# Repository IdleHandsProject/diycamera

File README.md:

# digiOBSCURA - A DIY Image Sensor and Digital Camera!

Check out the video!

Find the BOM for both boards here: https://www.findchips.com/org/10-open-hardware/list/162969-digiobscura-diy-image-sensor-and-digital-camera

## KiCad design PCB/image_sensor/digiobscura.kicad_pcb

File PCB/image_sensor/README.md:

# TEMPLATE KICAD PROJECT
## Sean Hodgins

If you're reading this, it means I have started a new project but have neglected to update the README file.
Please notify me of this by any means possible. 

Twitter: @idlehandsdev
Instagram: @idlehandsdev

Since you're reading this, go check out my YouTube Channel! http://youtube.com/seanhodginsfilms

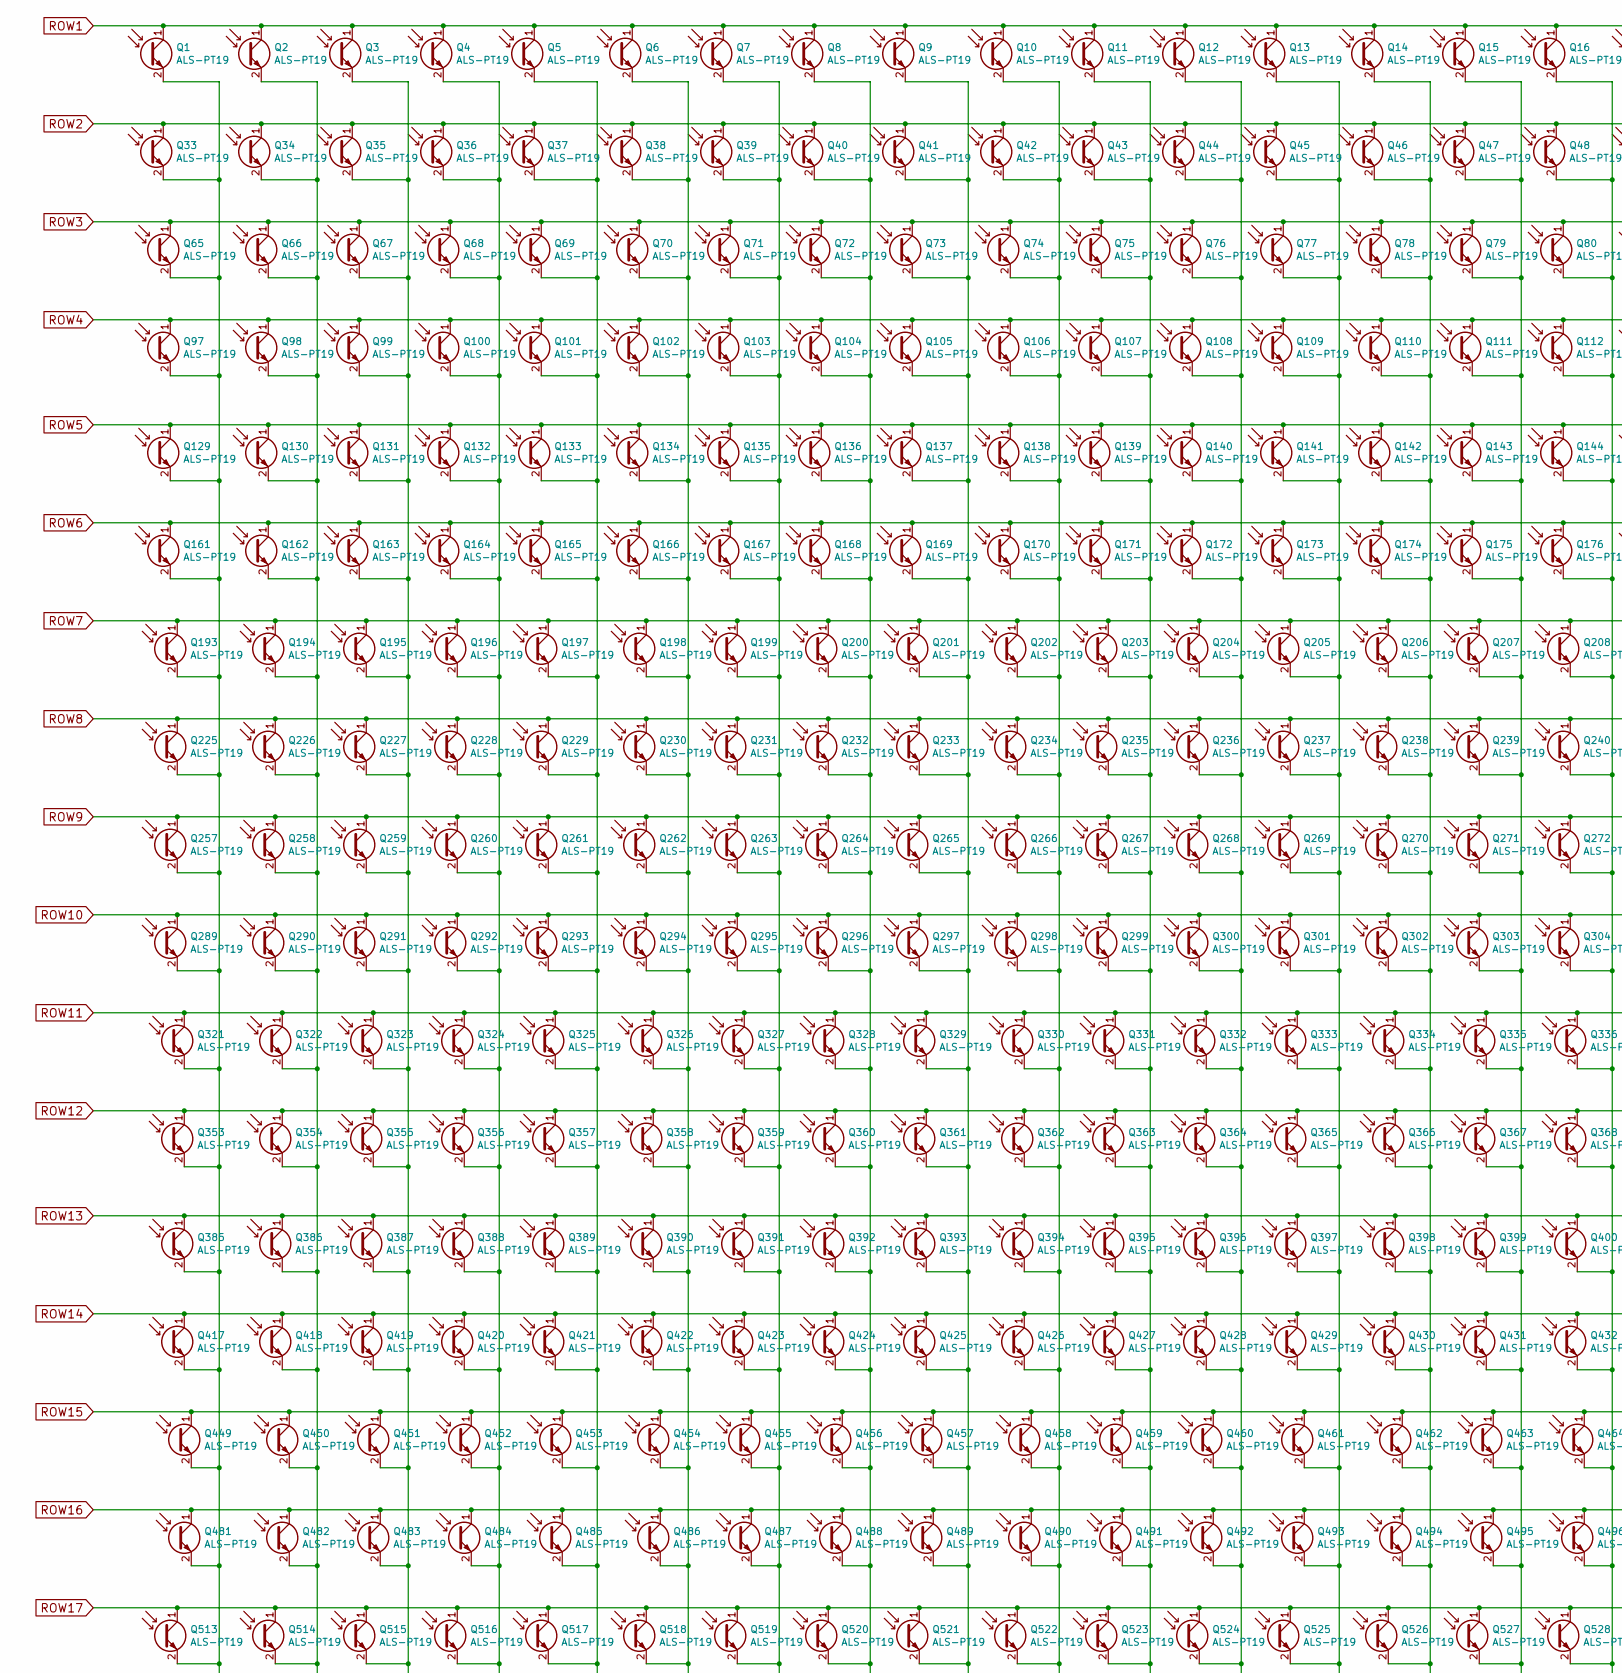
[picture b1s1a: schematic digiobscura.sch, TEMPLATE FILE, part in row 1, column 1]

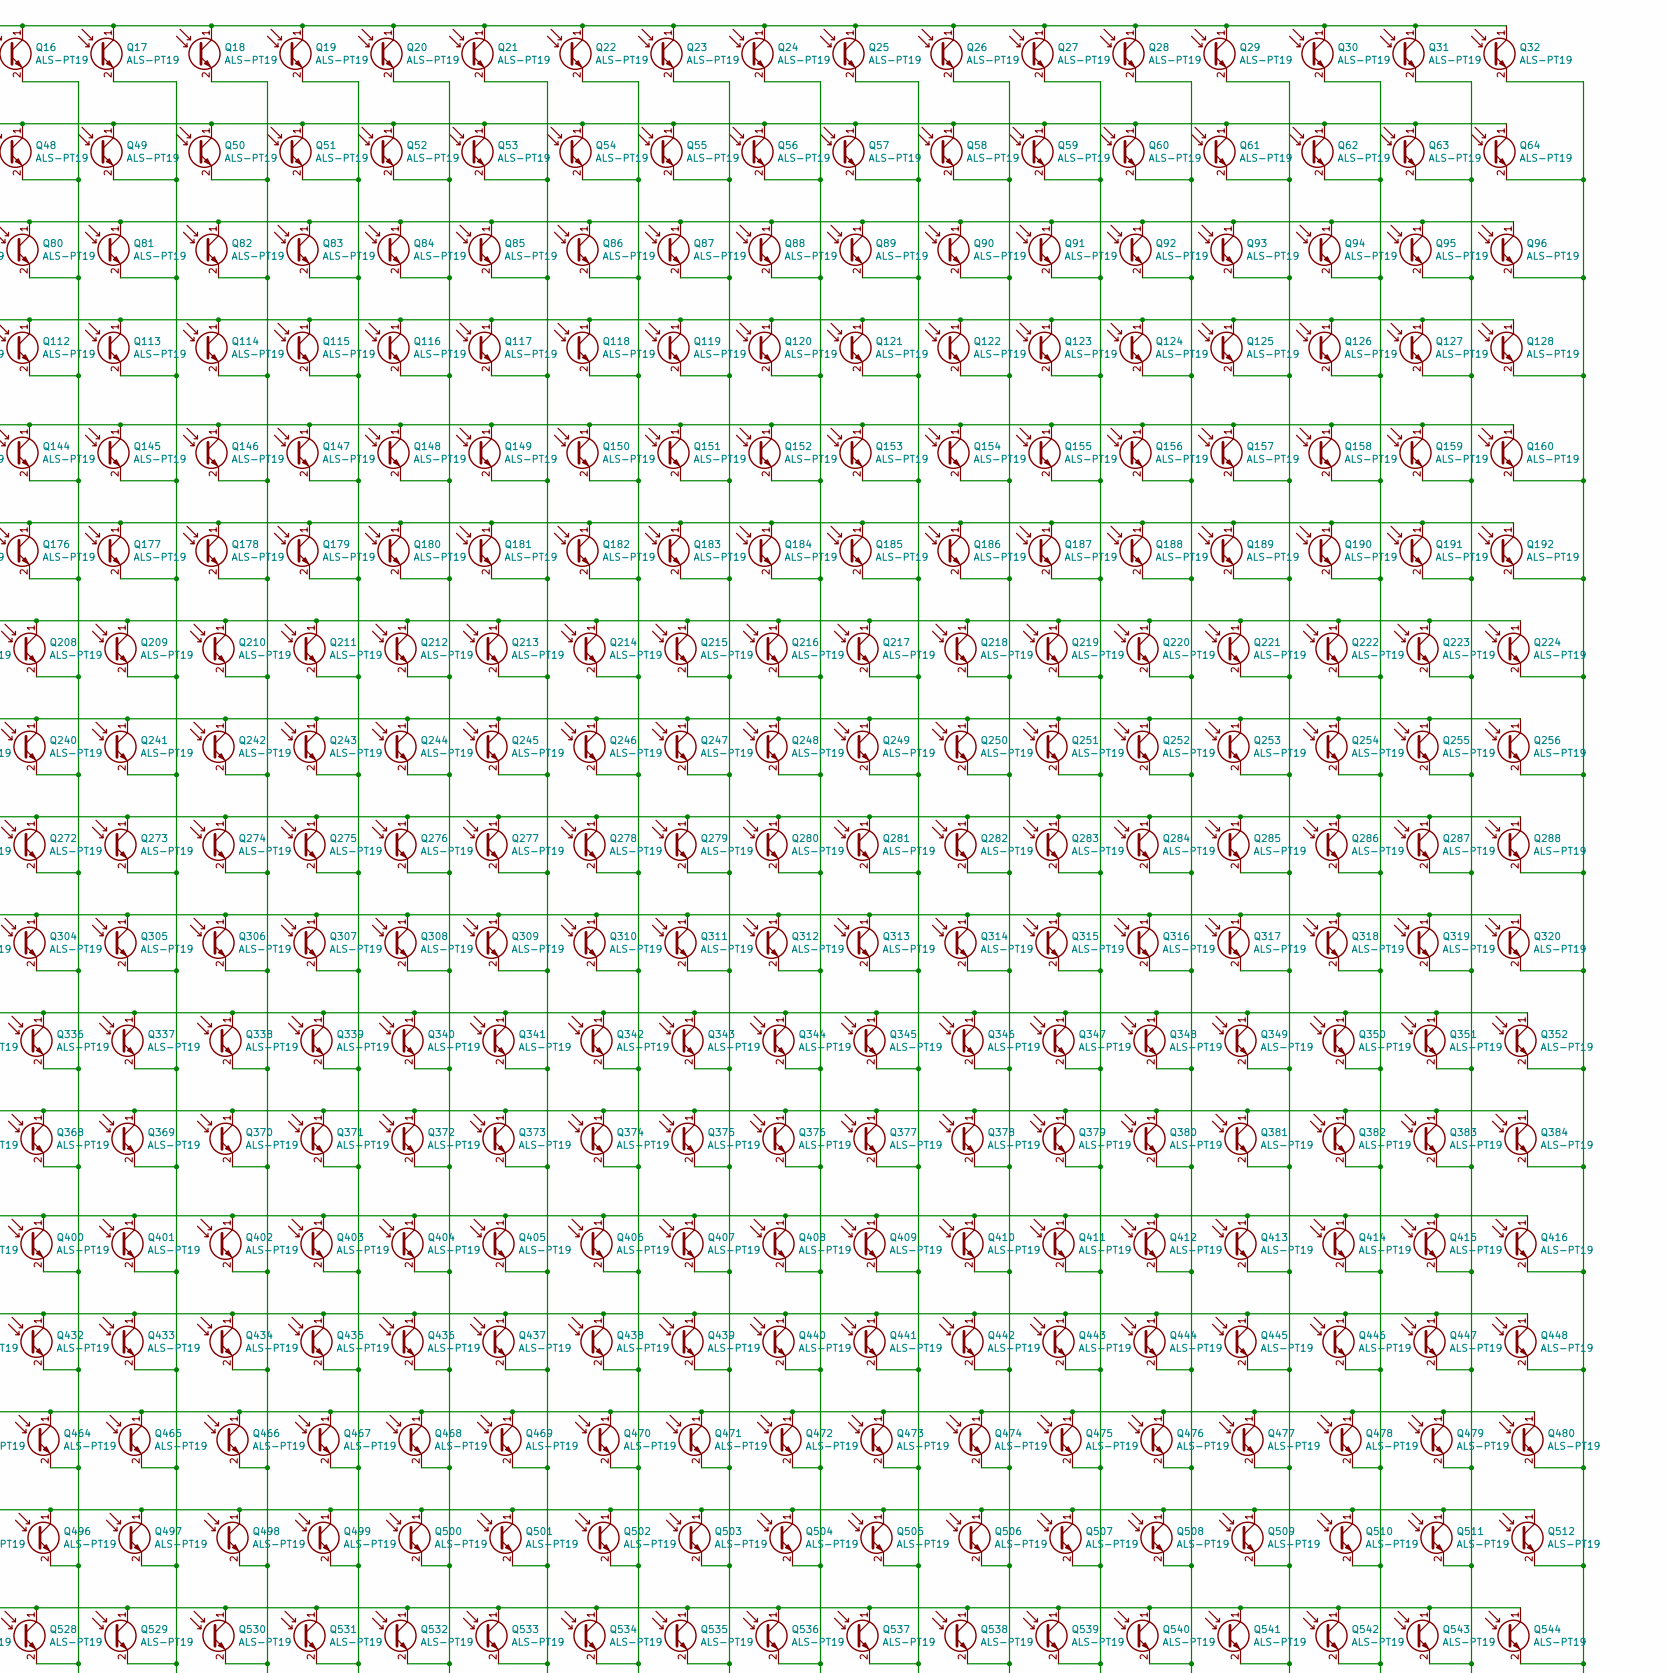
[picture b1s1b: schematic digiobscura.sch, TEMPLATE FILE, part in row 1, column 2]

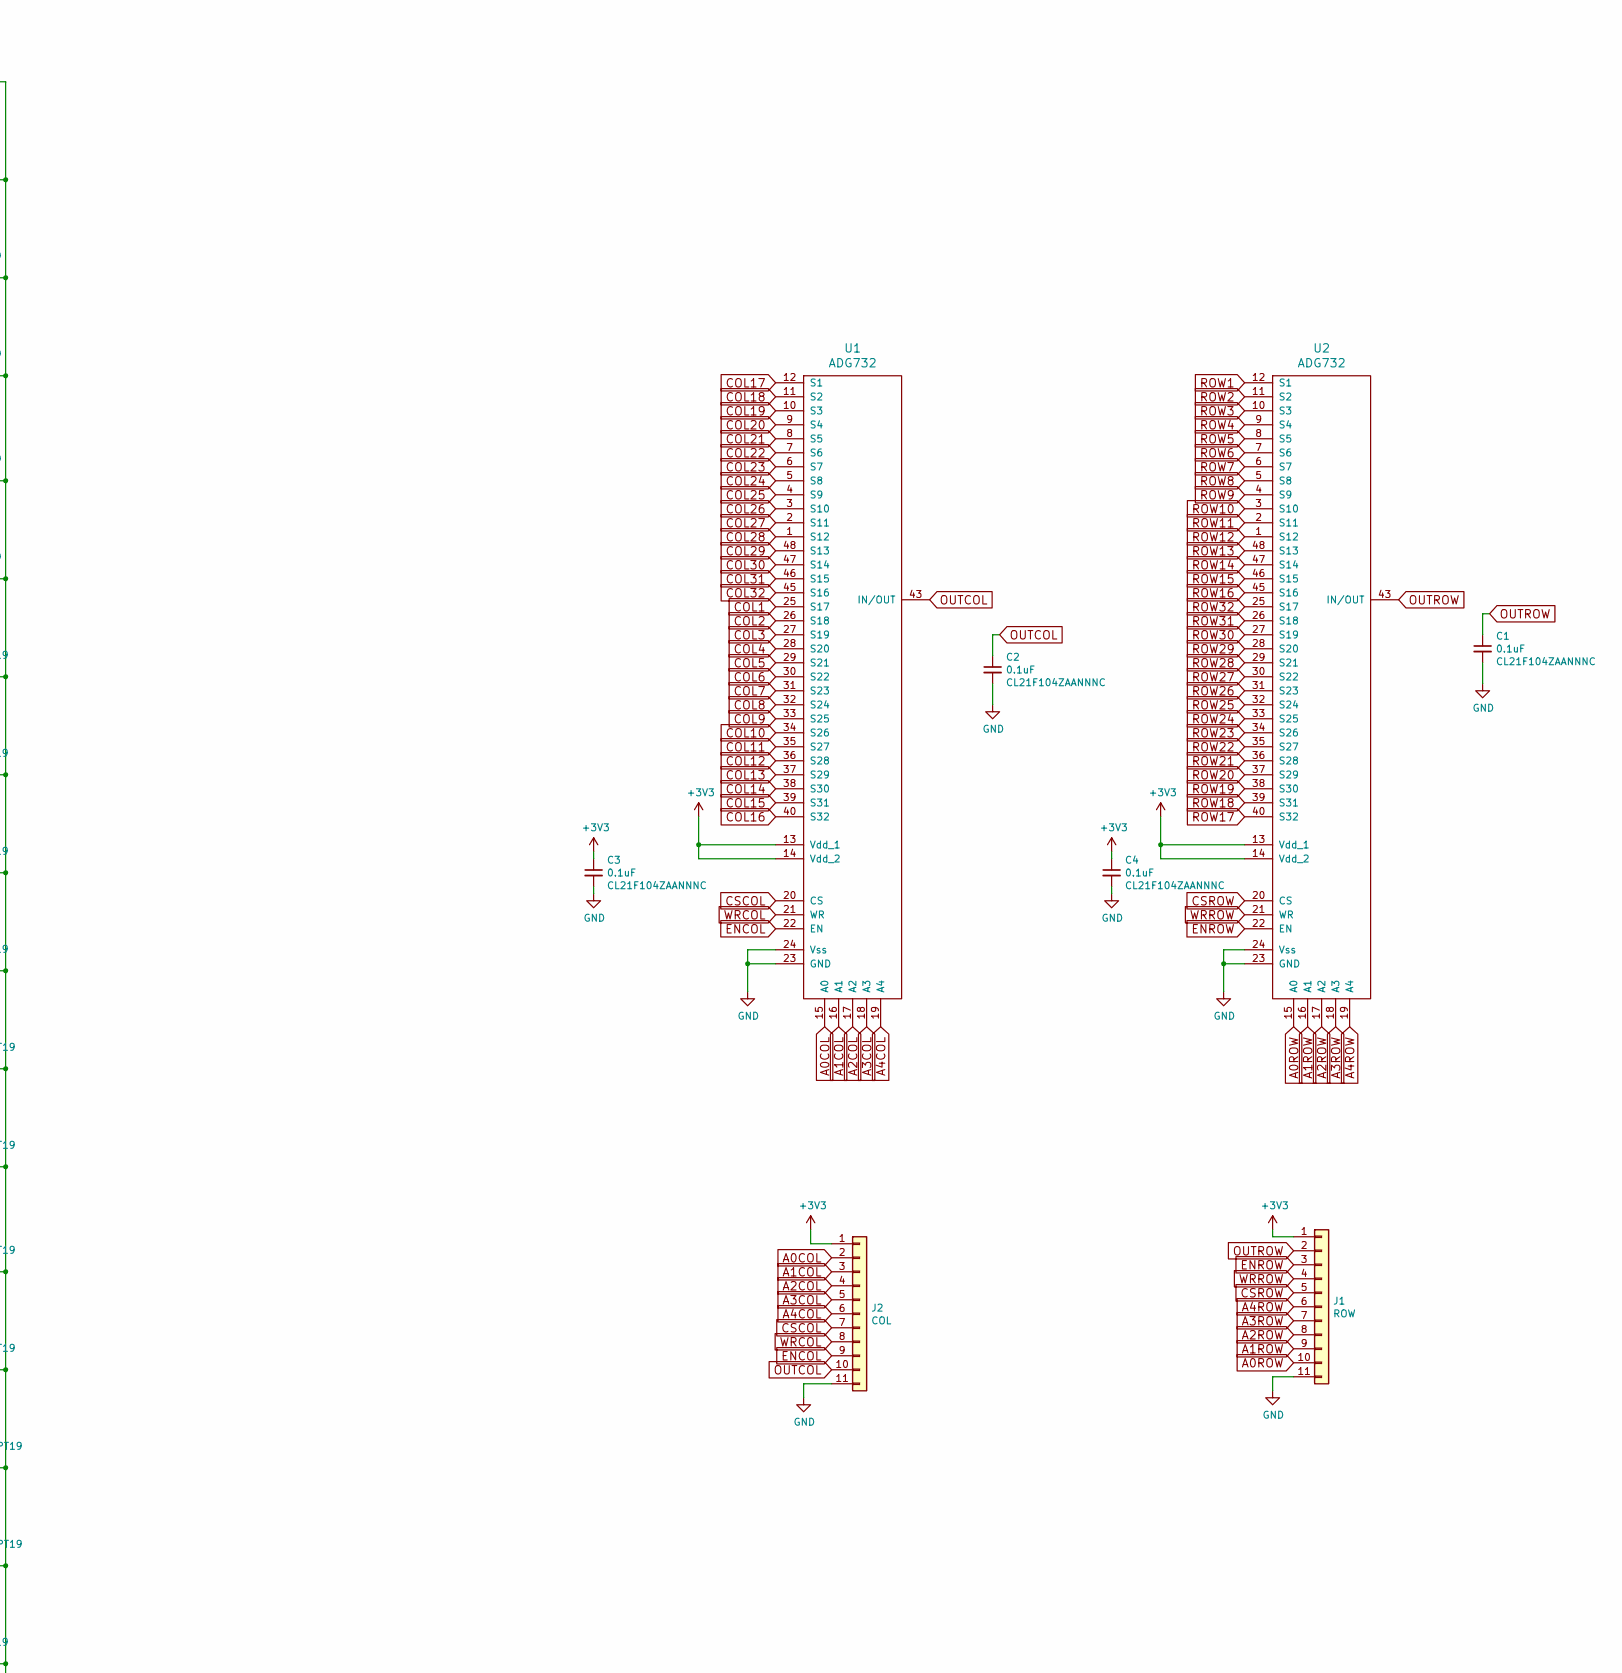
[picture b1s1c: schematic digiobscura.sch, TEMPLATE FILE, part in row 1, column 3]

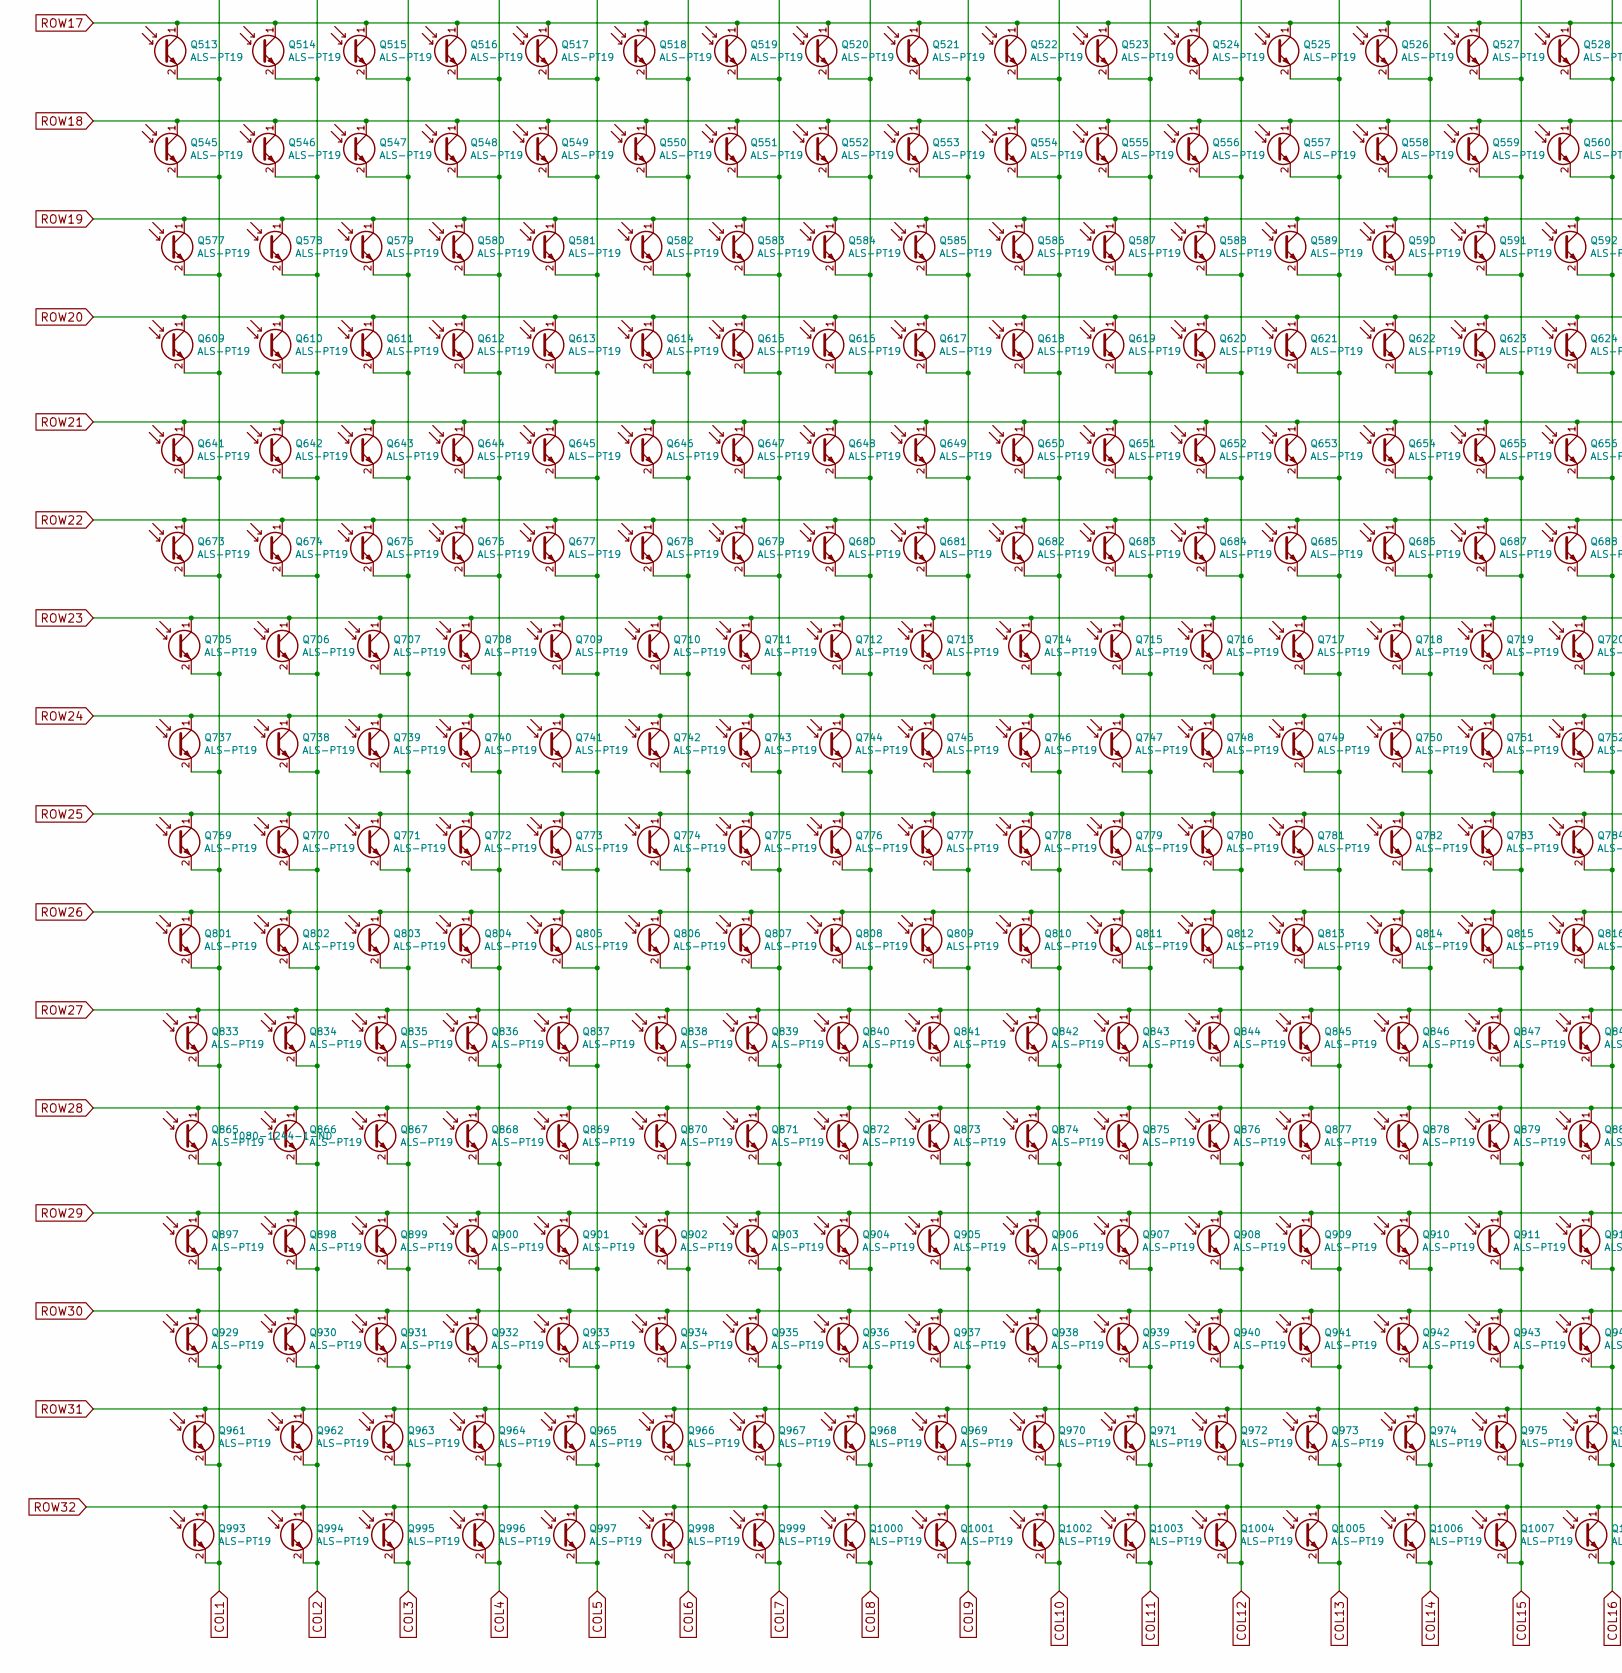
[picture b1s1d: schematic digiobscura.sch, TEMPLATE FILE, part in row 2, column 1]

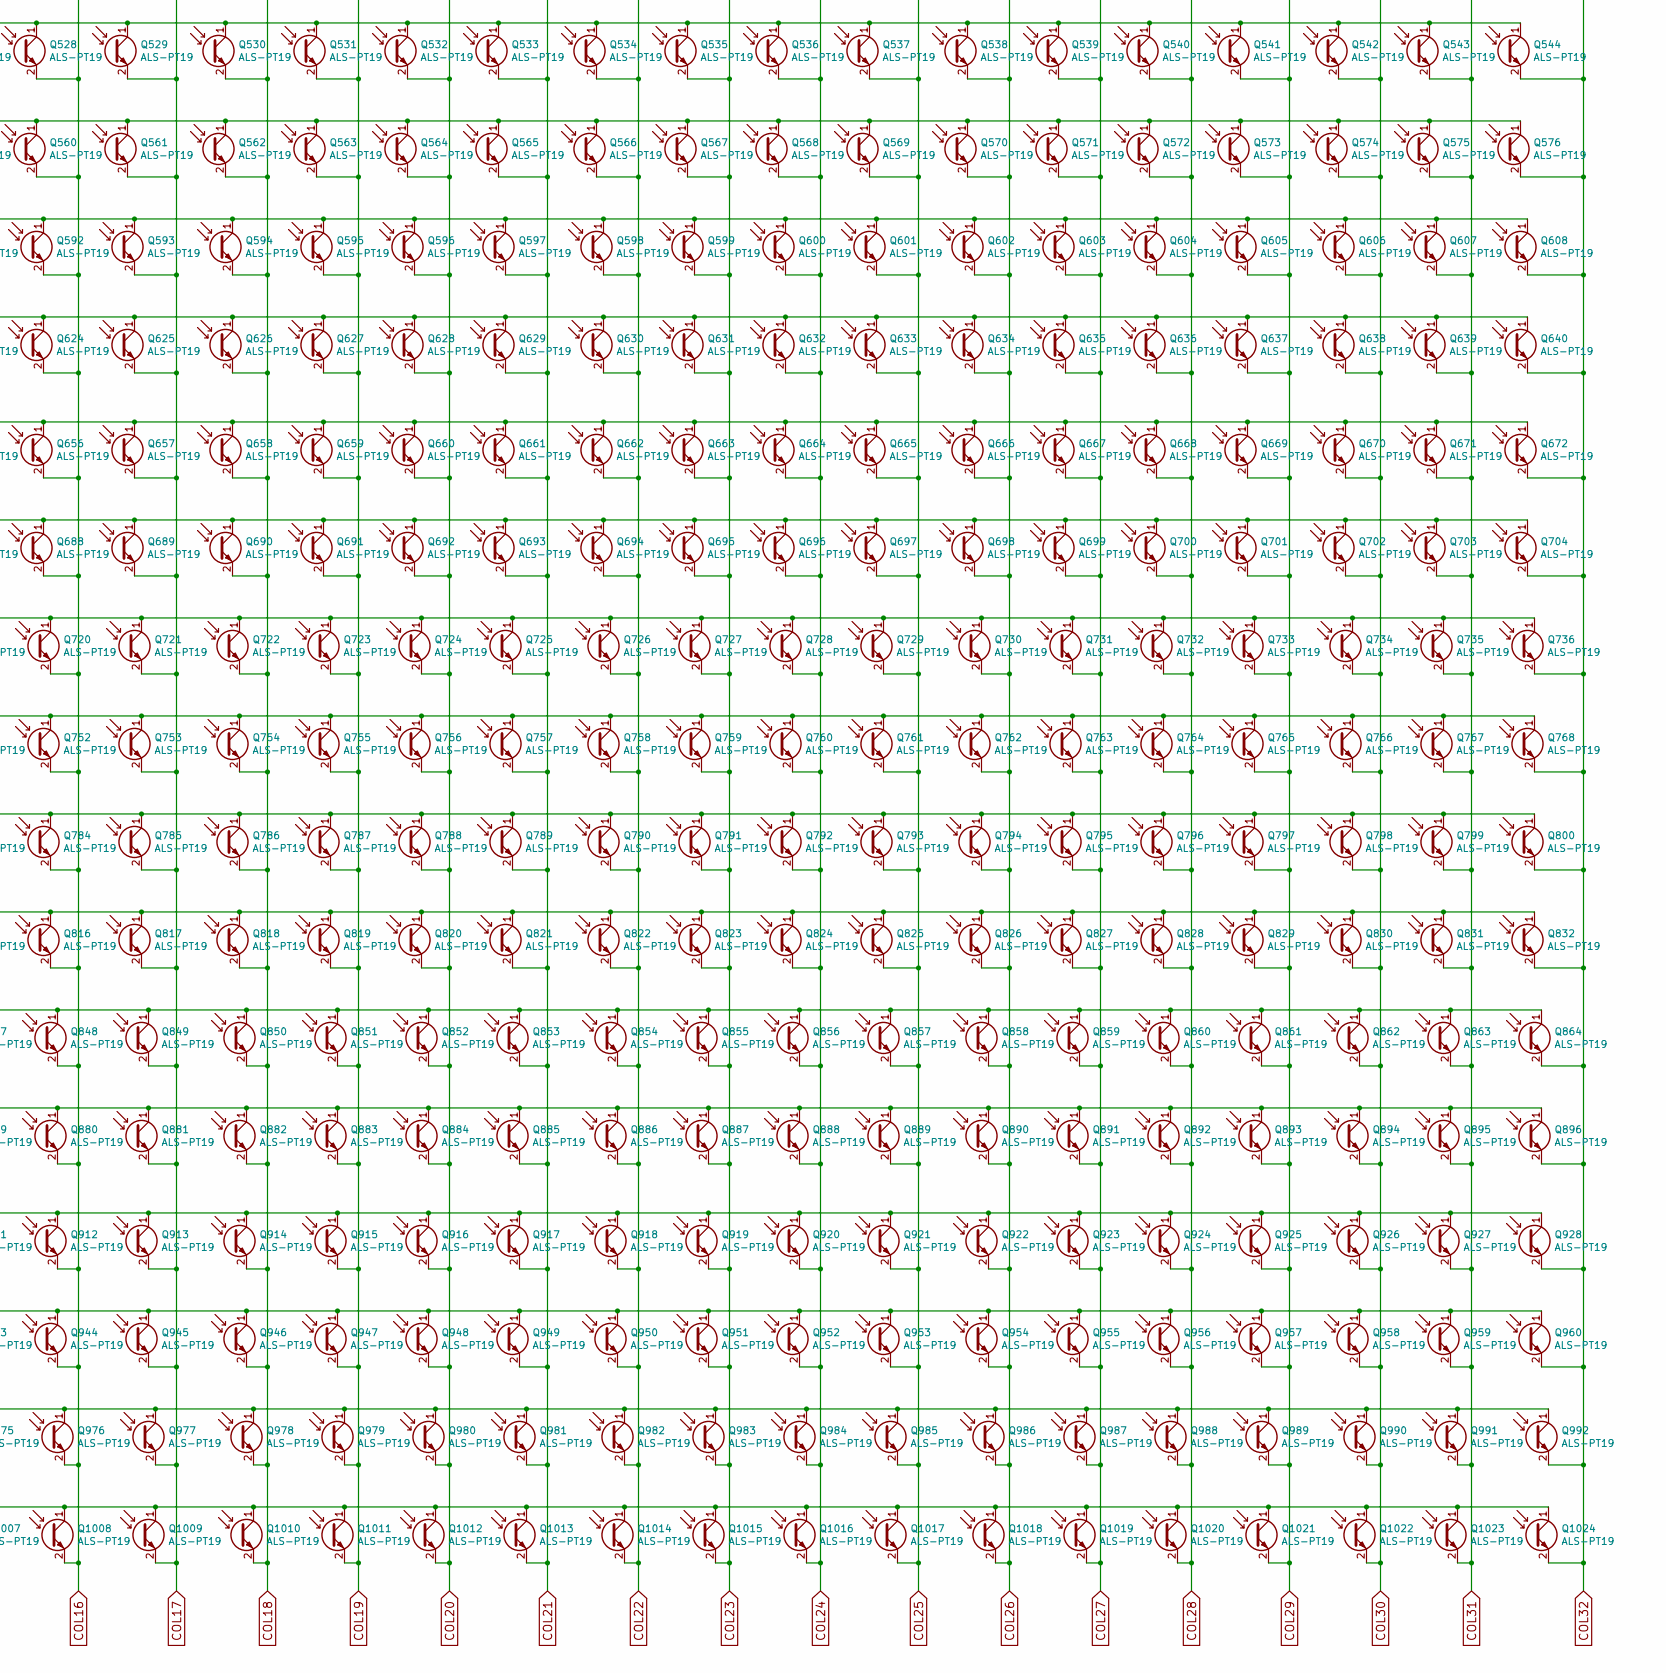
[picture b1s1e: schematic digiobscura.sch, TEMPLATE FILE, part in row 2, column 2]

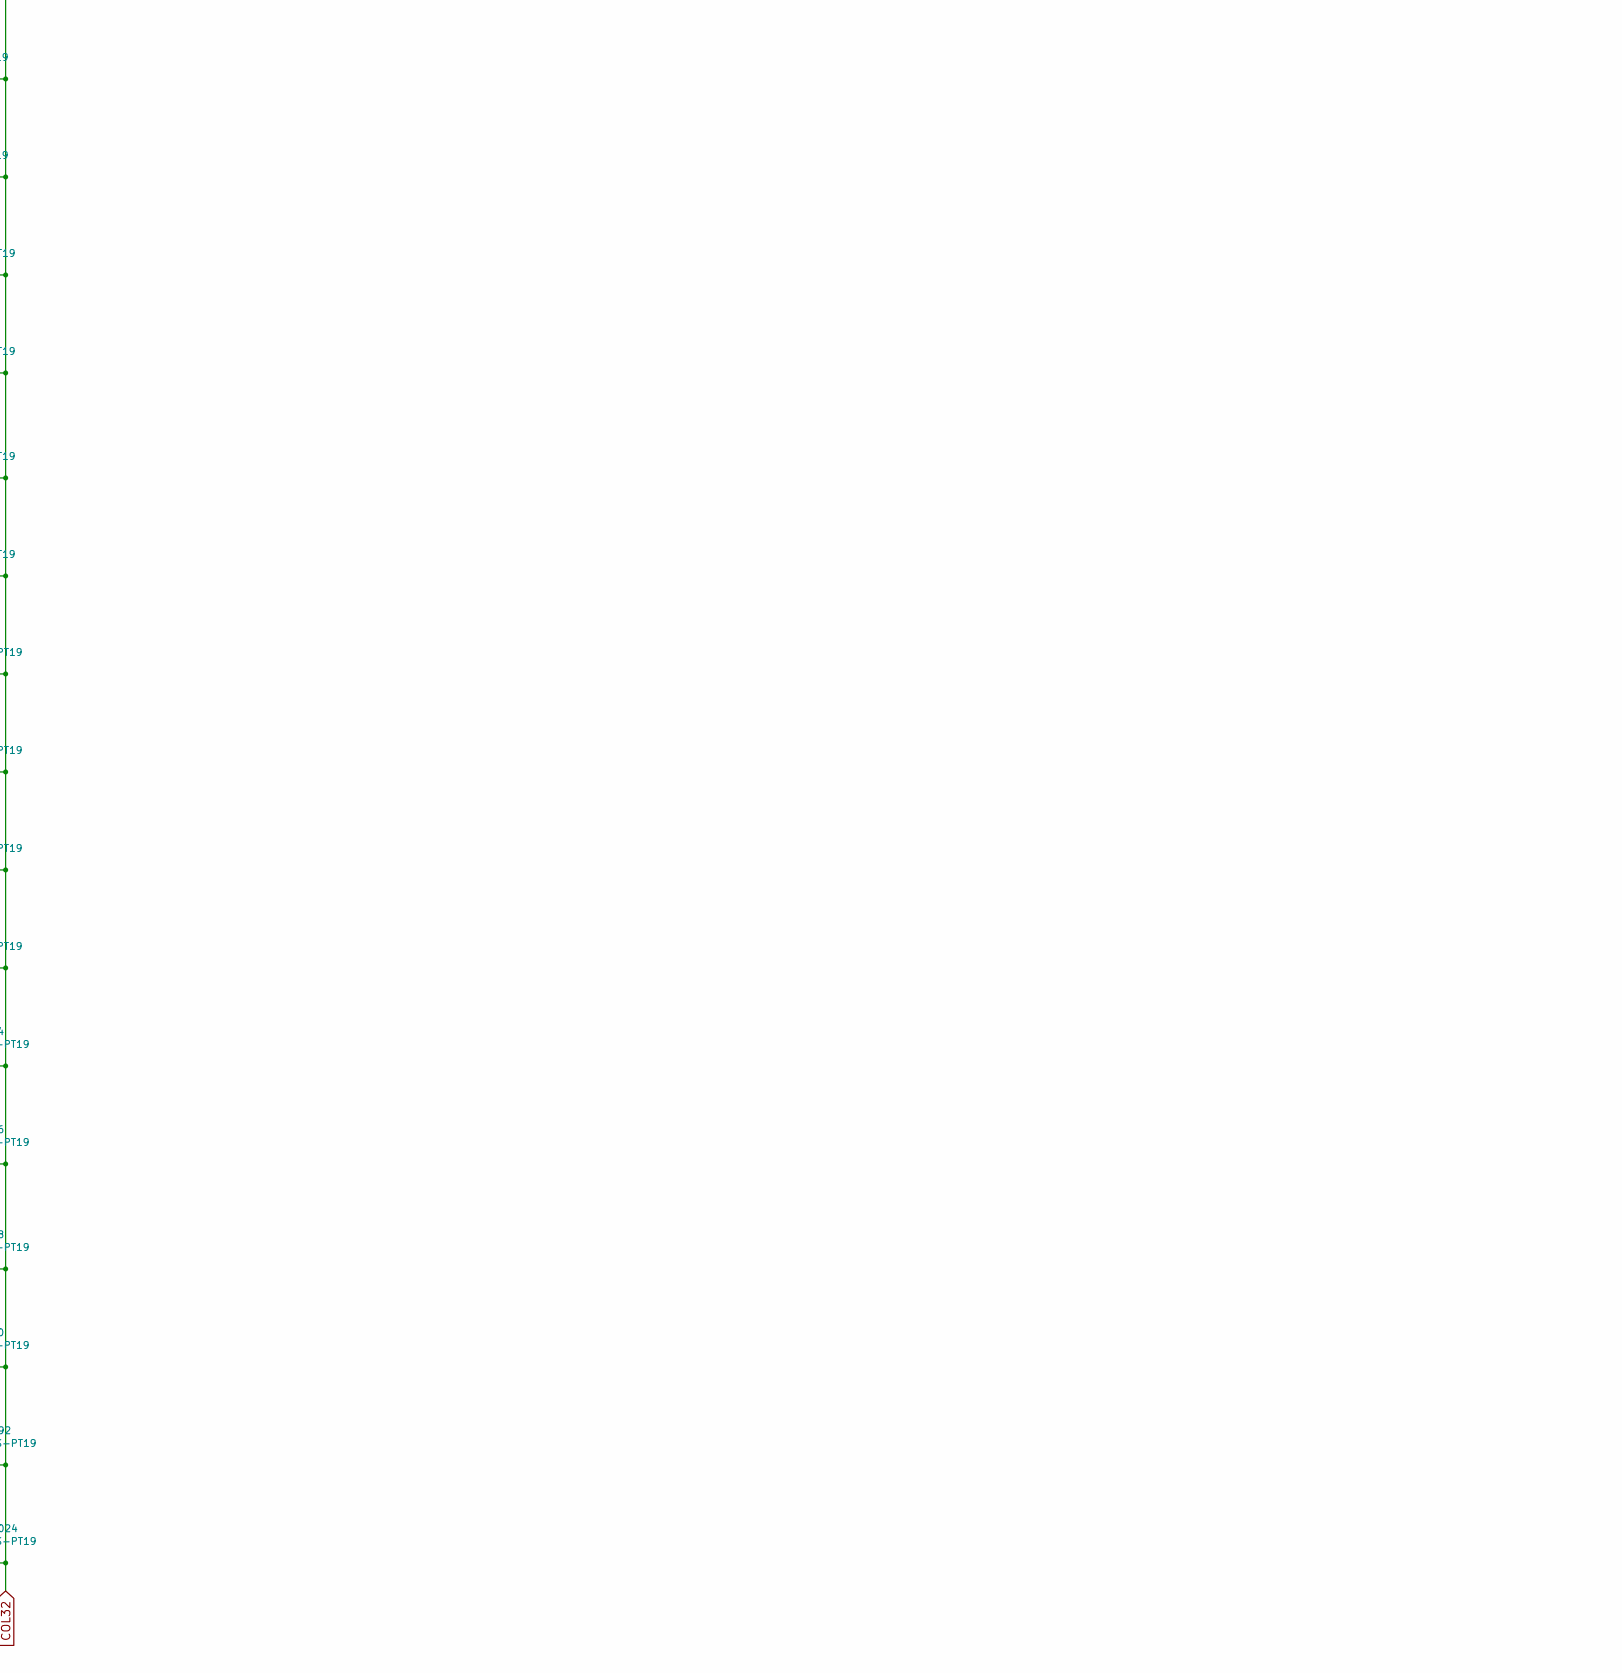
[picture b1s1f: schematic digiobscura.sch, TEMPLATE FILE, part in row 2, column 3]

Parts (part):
C1, C2, C3, C4: 0.1uF; C_0805_2012Metric; Digikey Part No. CL21F104ZAANNNC
J1: ROW; PinHeader_1x11_P2.54mm_Vertical; Digikey Part No. S7044-ND
J2: COL; PinHeader_1x11_P2.54mm_Vertical; Digikey Part No. S7044-ND
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
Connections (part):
+3V3: C3.1, C4.1, J1.1, J2.1, U1.13 (Vdd_1), U1.14 (Vdd_2), U2.13 (Vdd_1), U2.14 (Vdd_2)
A0COL: J2.2, U1.15 (A0)
A0ROW: J1.10, U2.15 (A0)
A1COL: J2.3, U1.16 (A1)
A1ROW: J1.9, U2.16 (A1)
A2COL: J2.4, U1.17 (A2)
A2ROW: J1.8, U2.17 (A2)
A3COL: J2.5, U1.18 (A3)
A3ROW: J1.7, U2.18 (A3)
A4COL: J2.6, U1.19 (A4)
A4ROW: J1.6, U2.19 (A4)
COL1: Q1.2 (E), Q33.2 (E), Q65.2 (E), Q97.2 (E), Q129.2 (E), Q161.2 (E), Q193.2 (E), Q225.2 (E), Q257.2 (E), Q289.2 (E), Q321.2 (E), Q353.2 (E), Q385.2 (E), Q417.2 (E), Q449.2 (E), Q481.2 (E), Q513.2 (E), Q545.2 (E), Q577.2 (E), Q609.2 (E), Q641.2 (E), Q673.2 (E), Q705.2 (E), Q737.2 (E), Q769.2 (E), Q801.2 (E), Q833.2 (E), Q865.2 (E), Q897.2 (E), Q929.2 (E), Q961.2 (E), Q993.2 (E), U1.25 (S17)
COL2: Q2.2 (E), Q34.2 (E), Q66.2 (E), Q98.2 (E), Q130.2 (E), Q162.2 (E), Q194.2 (E), Q226.2 (E), Q258.2 (E), Q290.2 (E), Q322.2 (E), Q354.2 (E), Q386.2 (E), Q418.2 (E), Q450.2 (E), Q482.2 (E), Q514.2 (E), Q546.2 (E), Q578.2 (E), Q610.2 (E), Q642.2 (E), Q674.2 (E), Q706.2 (E), Q738.2 (E), Q770.2 (E), Q802.2 (E), Q834.2 (E), Q866.2 (E), Q898.2 (E), Q930.2 (E), Q962.2 (E), Q994.2 (E), U1.26 (S18)
COL3: Q3.2 (E), Q35.2 (E), Q67.2 (E), Q99.2 (E), Q131.2 (E), Q163.2 (E), Q195.2 (E), Q227.2 (E), Q259.2 (E), Q291.2 (E), Q323.2 (E), Q355.2 (E), Q387.2 (E), Q419.2 (E), Q451.2 (E), Q483.2 (E), Q515.2 (E), Q547.2 (E), Q579.2 (E), Q611.2 (E), Q643.2 (E), Q675.2 (E), Q707.2 (E), Q739.2 (E), Q771.2 (E), Q803.2 (E), Q835.2 (E), Q867.2 (E), Q899.2 (E), Q931.2 (E), Q963.2 (E), Q995.2 (E), U1.27 (S19)
COL4: Q4.2 (E), Q36.2 (E), Q68.2 (E), Q100.2 (E), Q132.2 (E), Q164.2 (E), Q196.2 (E), Q228.2 (E), Q260.2 (E), Q292.2 (E), Q324.2 (E), Q356.2 (E), Q388.2 (E), Q420.2 (E), Q452.2 (E), Q484.2 (E), Q516.2 (E), Q548.2 (E), Q580.2 (E), Q612.2 (E), Q644.2 (E), Q676.2 (E), Q708.2 (E), Q740.2 (E), Q772.2 (E), Q804.2 (E), Q836.2 (E), Q868.2 (E), Q900.2 (E), Q932.2 (E), Q964.2 (E), Q996.2 (E), U1.28 (S20)
COL5: Q5.2 (E), Q37.2 (E), Q69.2 (E), Q101.2 (E), Q133.2 (E), Q165.2 (E), Q197.2 (E), Q229.2 (E), Q261.2 (E), Q293.2 (E), Q325.2 (E), Q357.2 (E), Q389.2 (E), Q421.2 (E), Q453.2 (E), Q485.2 (E), Q517.2 (E), Q549.2 (E), Q581.2 (E), Q613.2 (E), Q645.2 (E), Q677.2 (E), Q709.2 (E), Q741.2 (E), Q773.2 (E), Q805.2 (E), Q837.2 (E), Q869.2 (E), Q901.2 (E), Q933.2 (E), Q965.2 (E), Q997.2 (E), U1.29 (S21)
COL6: Q6.2 (E), Q38.2 (E), Q70.2 (E), Q102.2 (E), Q134.2 (E), Q166.2 (E), Q198.2 (E), Q230.2 (E), Q262.2 (E), Q294.2 (E), Q326.2 (E), Q358.2 (E), Q390.2 (E), Q422.2 (E), Q454.2 (E), Q486.2 (E), Q518.2 (E), Q550.2 (E), Q582.2 (E), Q614.2 (E), Q646.2 (E), Q678.2 (E), Q710.2 (E), Q742.2 (E), Q774.2 (E), Q806.2 (E), Q838.2 (E), Q870.2 (E), Q902.2 (E), Q934.2 (E), Q966.2 (E), Q998.2 (E), U1.30 (S22)
COL7: Q7.2 (E), Q39.2 (E), Q71.2 (E), Q103.2 (E), Q135.2 (E), Q167.2 (E), Q199.2 (E), Q231.2 (E), Q263.2 (E), Q295.2 (E), Q327.2 (E), Q359.2 (E), Q391.2 (E), Q423.2 (E), Q455.2 (E), Q487.2 (E), Q519.2 (E), Q551.2 (E), Q583.2 (E), Q615.2 (E), Q647.2 (E), Q679.2 (E), Q711.2 (E), Q743.2 (E), Q775.2 (E), Q807.2 (E), Q839.2 (E), Q871.2 (E), Q903.2 (E), Q935.2 (E), Q967.2 (E), Q999.2 (E), U1.31 (S23)
COL8: Q8.2 (E), Q40.2 (E), Q72.2 (E), Q104.2 (E), Q136.2 (E), Q168.2 (E), Q200.2 (E), Q232.2 (E), Q264.2 (E), Q296.2 (E), Q328.2 (E), Q360.2 (E), Q392.2 (E), Q424.2 (E), Q456.2 (E), Q488.2 (E), Q520.2 (E), Q552.2 (E), Q584.2 (E), Q616.2 (E), Q648.2 (E), Q680.2 (E), Q712.2 (E), Q744.2 (E), Q776.2 (E), Q808.2 (E), Q840.2 (E), Q872.2 (E), Q904.2 (E), Q936.2 (E), Q968.2 (E), Q1000.2 (E), U1.32 (S24)
COL9: Q9.2 (E), Q41.2 (E), Q73.2 (E), Q105.2 (E), Q137.2 (E), Q169.2 (E), Q201.2 (E), Q233.2 (E), Q265.2 (E), Q297.2 (E), Q329.2 (E), Q361.2 (E), Q393.2 (E), Q425.2 (E), Q457.2 (E), Q489.2 (E), Q521.2 (E), Q553.2 (E), Q585.2 (E), Q617.2 (E), Q649.2 (E), Q681.2 (E), Q713.2 (E), Q745.2 (E), Q777.2 (E), Q809.2 (E), Q841.2 (E), Q873.2 (E), Q905.2 (E), Q937.2 (E), Q969.2 (E), Q1001.2 (E), U1.33 (S25)
COL10: Q10.2 (E), Q42.2 (E), Q74.2 (E), Q106.2 (E), Q138.2 (E), Q170.2 (E), Q202.2 (E), Q234.2 (E), Q266.2 (E), Q298.2 (E), Q330.2 (E), Q362.2 (E), Q394.2 (E), Q426.2 (E), Q458.2 (E), Q490.2 (E), Q522.2 (E), Q554.2 (E), Q586.2 (E), Q618.2 (E), Q650.2 (E), Q682.2 (E), Q714.2 (E), Q746.2 (E), Q778.2 (E), Q810.2 (E), Q842.2 (E), Q874.2 (E), Q906.2 (E), Q938.2 (E), Q970.2 (E), Q1002.2 (E), U1.34 (S26)
COL11: Q11.2 (E), Q43.2 (E), Q75.2 (E), Q107.2 (E), Q139.2 (E), Q171.2 (E), Q203.2 (E), Q235.2 (E), Q267.2 (E), Q299.2 (E), Q331.2 (E), Q363.2 (E), Q395.2 (E), Q427.2 (E), Q459.2 (E), Q491.2 (E), Q523.2 (E), Q555.2 (E), Q587.2 (E), Q619.2 (E), Q651.2 (E), Q683.2 (E), Q715.2 (E), Q747.2 (E), Q779.2 (E), Q811.2 (E), Q843.2 (E), Q875.2 (E), Q907.2 (E), Q939.2 (E), Q971.2 (E), Q1003.2 (E), U1.35 (S27)
COL12: Q12.2 (E), Q44.2 (E), Q76.2 (E), Q108.2 (E), Q140.2 (E), Q172.2 (E), Q204.2 (E), Q236.2 (E), Q268.2 (E), Q300.2 (E), Q332.2 (E), Q364.2 (E), Q396.2 (E), Q428.2 (E), Q460.2 (E), Q492.2 (E), Q524.2 (E), Q556.2 (E), Q588.2 (E), Q620.2 (E), Q652.2 (E), Q684.2 (E), Q716.2 (E), Q748.2 (E), Q780.2 (E), Q812.2 (E), Q844.2 (E), Q876.2 (E), Q908.2 (E), Q940.2 (E), Q972.2 (E), Q1004.2 (E), U1.36 (S28)
COL13: Q13.2 (E), Q45.2 (E), Q77.2 (E), Q109.2 (E), Q141.2 (E), Q173.2 (E), Q205.2 (E), Q237.2 (E), Q269.2 (E), Q301.2 (E), Q333.2 (E), Q365.2 (E), Q397.2 (E), Q429.2 (E), Q461.2 (E), Q493.2 (E), Q525.2 (E), Q557.2 (E), Q589.2 (E), Q621.2 (E), Q653.2 (E), Q685.2 (E), Q717.2 (E), Q749.2 (E), Q781.2 (E), Q813.2 (E), Q845.2 (E), Q877.2 (E), Q909.2 (E), Q941.2 (E), Q973.2 (E), Q1005.2 (E), U1.37 (S29)
COL14: Q14.2 (E), Q46.2 (E), Q78.2 (E), Q110.2 (E), Q142.2 (E), Q174.2 (E), Q206.2 (E), Q238.2 (E), Q270.2 (E), Q302.2 (E), Q334.2 (E), Q366.2 (E), Q398.2 (E), Q430.2 (E), Q462.2 (E), Q494.2 (E), Q526.2 (E), Q558.2 (E), Q590.2 (E), Q622.2 (E), Q654.2 (E), Q686.2 (E), Q718.2 (E), Q750.2 (E), Q782.2 (E), Q814.2 (E), Q846.2 (E), Q878.2 (E), Q910.2 (E), Q942.2 (E), Q974.2 (E), Q1006.2 (E), U1.38 (S30)
COL15: Q15.2 (E), Q47.2 (E), Q79.2 (E), Q111.2 (E), Q143.2 (E), Q175.2 (E), Q207.2 (E), Q239.2 (E), Q271.2 (E), Q303.2 (E), Q335.2 (E), Q367.2 (E), Q399.2 (E), Q431.2 (E), Q463.2 (E), Q495.2 (E), Q527.2 (E), Q559.2 (E), Q591.2 (E), Q623.2 (E), Q655.2 (E), Q687.2 (E), Q719.2 (E), Q751.2 (E), Q783.2 (E), Q815.2 (E), Q847.2 (E), Q879.2 (E), Q911.2 (E), Q943.2 (E), Q975.2 (E), Q1007.2 (E), U1.39 (S31)
COL16: Q16.2 (E), Q48.2 (E), Q80.2 (E), Q112.2 (E), Q144.2 (E), Q176.2 (E), Q208.2 (E), Q240.2 (E), Q272.2 (E), Q304.2 (E), Q336.2 (E), Q368.2 (E), Q400.2 (E), Q432.2 (E), Q464.2 (E), Q496.2 (E), Q528.2 (E), Q560.2 (E), Q592.2 (E), Q624.2 (E), Q656.2 (E), Q688.2 (E), Q720.2 (E), Q752.2 (E), Q784.2 (E), Q816.2 (E), Q848.2 (E), Q880.2 (E), Q912.2 (E), Q944.2 (E), Q976.2 (E), Q1008.2 (E), U1.40 (S32)
COL17: Q17.2 (E), Q49.2 (E), Q81.2 (E), Q113.2 (E), Q145.2 (E), Q177.2 (E), Q209.2 (E), Q241.2 (E), Q273.2 (E), Q305.2 (E), Q337.2 (E), Q369.2 (E), Q401.2 (E), Q433.2 (E), Q465.2 (E), Q497.2 (E), Q529.2 (E), Q561.2 (E), Q593.2 (E), Q625.2 (E), Q657.2 (E), Q689.2 (E), Q721.2 (E), Q753.2 (E), Q785.2 (E), Q817.2 (E), Q849.2 (E), Q881.2 (E), Q913.2 (E), Q945.2 (E), Q977.2 (E), Q1009.2 (E), U1.12 (S1)
COL18: Q18.2 (E), Q50.2 (E), Q82.2 (E), Q114.2 (E), Q146.2 (E), Q178.2 (E), Q210.2 (E), Q242.2 (E), Q274.2 (E), Q306.2 (E), Q338.2 (E), Q370.2 (E), Q402.2 (E), Q434.2 (E), Q466.2 (E), Q498.2 (E), Q530.2 (E), Q562.2 (E), Q594.2 (E), Q626.2 (E), Q658.2 (E), Q690.2 (E), Q722.2 (E), Q754.2 (E), Q786.2 (E), Q818.2 (E), Q850.2 (E), Q882.2 (E), Q914.2 (E), Q946.2 (E), Q978.2 (E), Q1010.2 (E), U1.11 (S2)
COL19: Q19.2 (E), Q51.2 (E), Q83.2 (E), Q115.2 (E), Q147.2 (E), Q179.2 (E), Q211.2 (E), Q243.2 (E), Q275.2 (E), Q307.2 (E), Q339.2 (E), Q371.2 (E), Q403.2 (E), Q435.2 (E), Q467.2 (E), Q499.2 (E), Q531.2 (E), Q563.2 (E), Q595.2 (E), Q627.2 (E), Q659.2 (E), Q691.2 (E), Q723.2 (E), Q755.2 (E), Q787.2 (E), Q819.2 (E), Q851.2 (E), Q883.2 (E), Q915.2 (E), Q947.2 (E), Q979.2 (E), Q1011.2 (E), U1.10 (S3)
COL20: Q20.2 (E), Q52.2 (E), Q84.2 (E), Q116.2 (E), Q148.2 (E), Q180.2 (E), Q212.2 (E), Q244.2 (E), Q276.2 (E), Q308.2 (E), Q340.2 (E), Q372.2 (E), Q404.2 (E), Q436.2 (E), Q468.2 (E), Q500.2 (E), Q532.2 (E), Q564.2 (E), Q596.2 (E), Q628.2 (E), Q660.2 (E), Q692.2 (E), Q724.2 (E), Q756.2 (E), Q788.2 (E), Q820.2 (E), Q852.2 (E), Q884.2 (E), Q916.2 (E), Q948.2 (E), Q980.2 (E), Q1012.2 (E), U1.9 (S4)
COL21: Q21.2 (E), Q53.2 (E), Q85.2 (E), Q117.2 (E), Q149.2 (E), Q181.2 (E), Q213.2 (E), Q245.2 (E), Q277.2 (E), Q309.2 (E), Q341.2 (E), Q373.2 (E), Q405.2 (E), Q437.2 (E), Q469.2 (E), Q501.2 (E), Q533.2 (E), Q565.2 (E), Q597.2 (E), Q629.2 (E), Q661.2 (E), Q693.2 (E), Q725.2 (E), Q757.2 (E), Q789.2 (E), Q821.2 (E), Q853.2 (E), Q885.2 (E), Q917.2 (E), Q949.2 (E), Q981.2 (E), Q1013.2 (E), U1.8 (S5)
COL22: Q22.2 (E), Q54.2 (E), Q86.2 (E), Q118.2 (E), Q150.2 (E), Q182.2 (E), Q214.2 (E), Q246.2 (E), Q278.2 (E), Q310.2 (E), Q342.2 (E), Q374.2 (E), Q406.2 (E), Q438.2 (E), Q470.2 (E), Q502.2 (E), Q534.2 (E), Q566.2 (E), Q598.2 (E), Q630.2 (E), Q662.2 (E), Q694.2 (E), Q726.2 (E), Q758.2 (E), Q790.2 (E), Q822.2 (E), Q854.2 (E), Q886.2 (E), Q918.2 (E), Q950.2 (E), Q982.2 (E), Q1014.2 (E), U1.7 (S6)
COL23: Q23.2 (E), Q55.2 (E), Q87.2 (E), Q119.2 (E), Q151.2 (E), Q183.2 (E), Q215.2 (E), Q247.2 (E), Q279.2 (E), Q311.2 (E), Q343.2 (E), Q375.2 (E), Q407.2 (E), Q439.2 (E), Q471.2 (E), Q503.2 (E), Q535.2 (E), Q567.2 (E), Q599.2 (E), Q631.2 (E), Q663.2 (E), Q695.2 (E), Q727.2 (E), Q759.2 (E), Q791.2 (E), Q823.2 (E), Q855.2 (E), Q887.2 (E), Q919.2 (E), Q951.2 (E), Q983.2 (E), Q1015.2 (E), U1.6 (S7)
COL24: Q24.2 (E), Q56.2 (E), Q88.2 (E), Q120.2 (E), Q152.2 (E), Q184.2 (E), Q216.2 (E), Q248.2 (E), Q280.2 (E), Q312.2 (E), Q344.2 (E), Q376.2 (E), Q408.2 (E), Q440.2 (E), Q472.2 (E), Q504.2 (E), Q536.2 (E), Q568.2 (E), Q600.2 (E), Q632.2 (E), Q664.2 (E), Q696.2 (E), Q728.2 (E), Q760.2 (E), Q792.2 (E), Q824.2 (E), Q856.2 (E), Q888.2 (E), Q920.2 (E), Q952.2 (E), Q984.2 (E), Q1016.2 (E), U1.5 (S8)
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
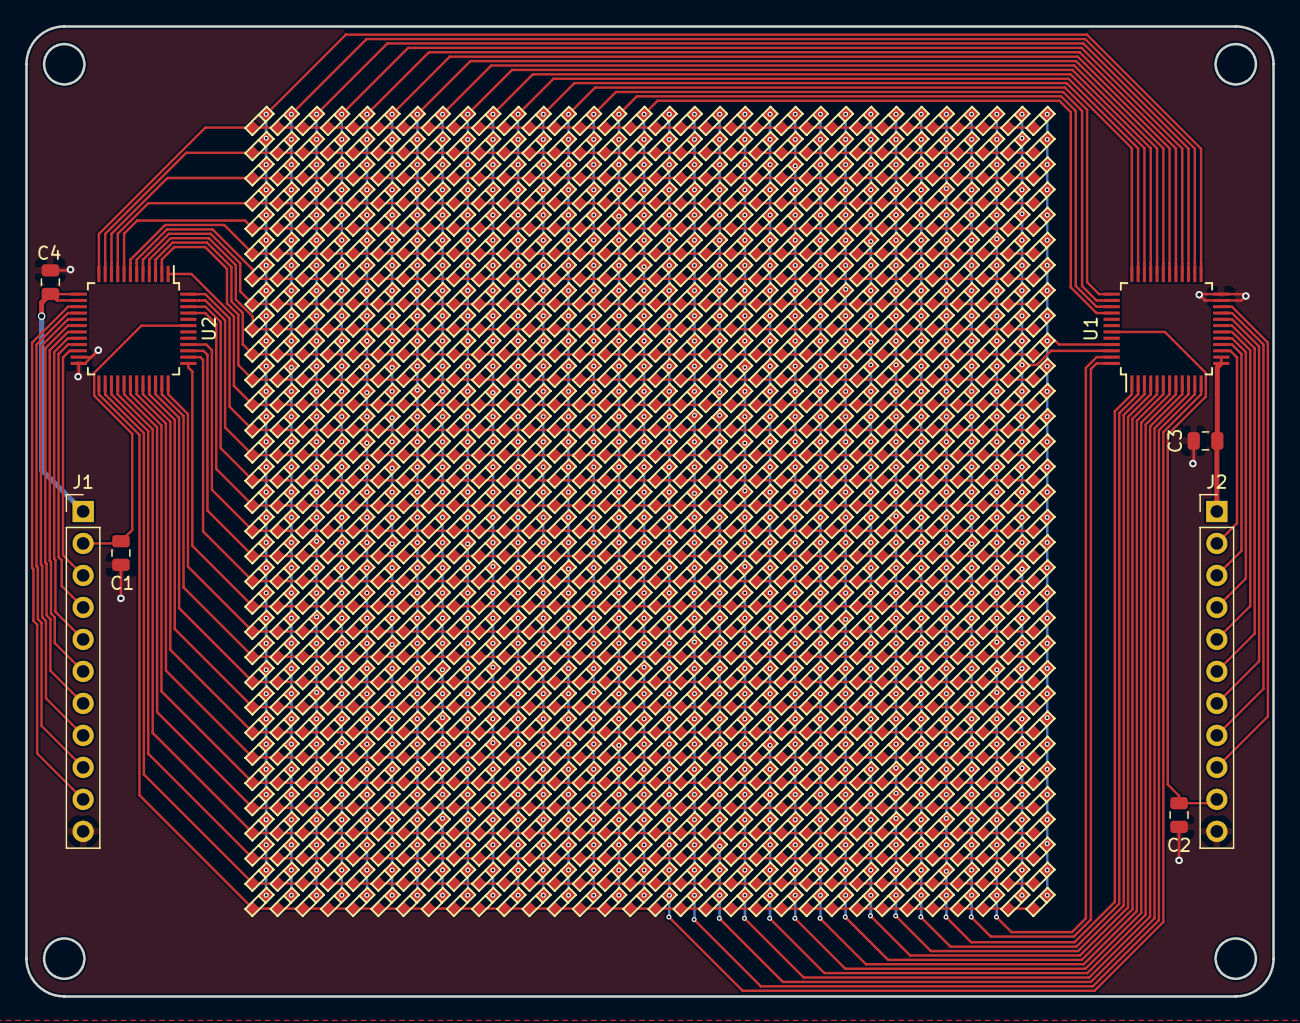
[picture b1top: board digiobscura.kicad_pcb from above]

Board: 2 copper layers, 99.0 x 77.0 mm, 1032 parts (0 on the bottom side), 84 nets.
